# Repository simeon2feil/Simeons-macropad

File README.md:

hi this is my steam deck or macropad its just like a steam deck but a lot cheaper all files like the scematic ar in the main page pls  aprove it this time 

https://github.com/simeon2feil/Simeons-macropad/blob/main/macropad%20v4%20case%20main%20body.FCStd

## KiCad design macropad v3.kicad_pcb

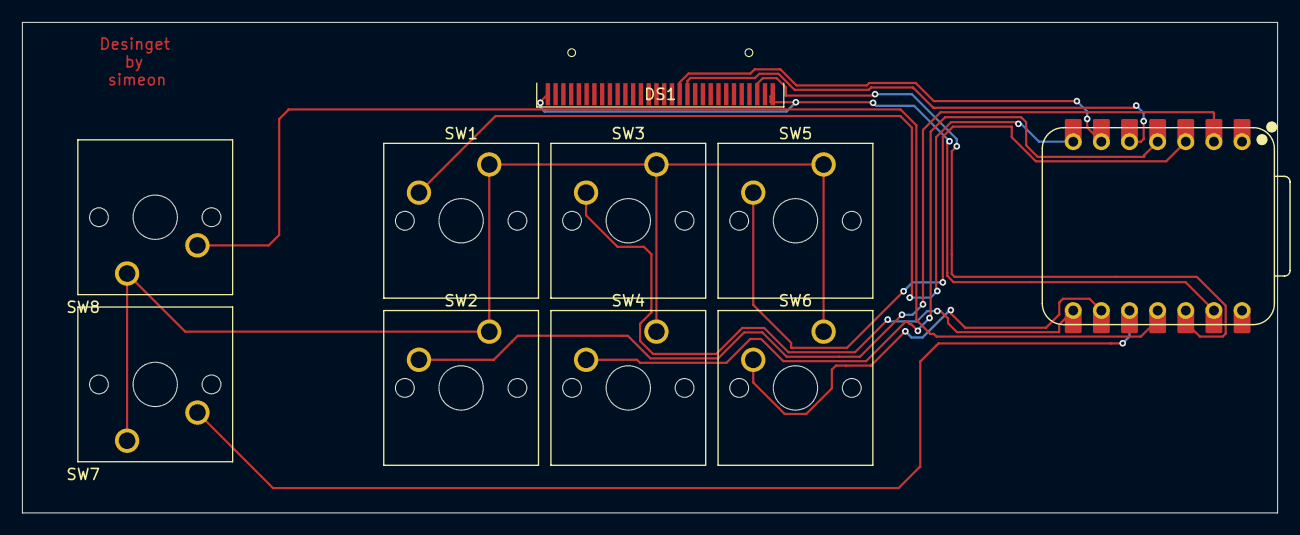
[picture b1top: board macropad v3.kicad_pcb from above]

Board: 2 copper layers, 113.3 x 44.3 mm, 10 parts (0 on the bottom side), 13 nets.

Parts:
DS1: OLED-128O064D
SW1, SW2, SW3, SW4, SW5, SW6, SW7, SW8: SW_Push; SW_Cherry_MX_1.00u_PCB
U1: XIAO-RP2040-DIP

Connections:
GND: SW1.1, SW2.1, SW3.1, SW4.1, SW5.1, SW6.1, SW7.1, SW8.1
unnamed: DS1.18 (D0), U1.6 (GPIO7/SCL)
unnamed: DS1.19 (D1), U1.5 (GPIO6/SDA)
unnamed: DS1.28 (VCC), U1.12 (3V3)
unnamed: DS1.1 (GND), DS1.30 (GND), U1.13 (GND)
unnamed: SW1.2, U1.7 (GPIO0/TX)
unnamed: SW3.2, U1.8 (GPIO1/RX)
unnamed: SW6.2, U1.9 (GPIO2/SCK)
unnamed: SW8.2, U1.11 (GPIO3/MOSI)
unnamed: SW7.2, U1.10 (GPIO4/MISO)
unnamed: SW2.2, U1.2 (GPIO27/ADC1/A1)
unnamed: SW5.2, U1.3 (GPIO28/ADC2/A2)
unnamed: SW4.2, U1.4 (GPIO29/ADC3/A3)

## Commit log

2025-12-06 this is V4 of may macropad
